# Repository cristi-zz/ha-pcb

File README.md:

## Home automation PCB

The story behind this, can be found [on my blog](https://visoft.ro/hello/expanding-the-stack-designing-a-pcb/2023/01/11/)

It will hold a series of breakout boards for I2C IO expanders, 1Wire drivers, ADCs. All are controlled with a Raspberry Pi 3B+.

The 220V actuators are controlled by a board with 16 mechanical relays. The board is in turn controlled by PCF8575 chip that takes I2C commands and controls 16 I/O pins. Board is active on low (optocouplers), PCF8575 can sink more current (than it could source). Perfect match.

The 16 relay board is separate, from this PCB, only a pin header connection is made.

The temperature sensors are DS18B20 that work on 1 wire protocol. These are already mounted with Ethernet cables terminated with RJ45. The sensors are read/driven by 4 ds2482s-100 chips (RJ45 terminals and ds2482s-100 are on this PCB).
The RJ jacks must be galvanic!

There are some other relays/contactors/voltages that needs monitoring, all done by 2 ADS1115 16-Bit ADC, present on board.

The chips are already sourced and live on their breakout boards. The PCB is mainly THT because of sourcing issues (eg can't find ds2482s-100 anywhere, will reuse existing breakouts). Only SMD are the 3.5 audio jacks (for ADC) again because no THT could be sourced atm.

The Raspberry Pi connector is only 20 pin wide because only the first few are used (5V, 3.3, SDA, SCL, GND)

There is a spurious bug, all relays are ON when the 16 relay board is powered but the Raspberry (that powers the rest of the circuits) is OFF. So, a solid state relay is used to cut power to the relay board when the RaPi is shutted down.

With the exception of ADCs, the schema and design choices follow the existing (4 years old) system.

This repo is mainly for reviewing purposes.

**The story behind this PCB is on [www.visoft.ro](https://www.visoft.ro/beginner/expanding-the-stack-designing-a-pcb/2372/)**

A list with the devices

### Relay board that will be driven:
https://www.sainsmart.com/products/16-channel-12v-relay-module

### 16 channel IO expander that will drive the board:
https://www.artekit.eu/products/breakout-boards/io/ak-pcf8575-i2c-16-bit-io-expander-breakout/

### I2C level shifter (3.3 to 5V)
https://www.pololu.com/product/2595

### I2C to differential signals:
https://www.sparkfun.com/products/retired/14589

### 1Wire drivers:
https://www.artekit.eu/products/breakout-boards/io/ak-ds2482s-100/

### ADC:
https://www.adafruit.com/product/1085

Some ADC "watch" only for presence/absence of 5V power but some are listenting to CT sensors.
Quasi similar model: https://www.seeedstudio.com/Non-invasive-AC-Current-Sensor-30A-ma-p-519.html

### Solid state relay:
https://www.tme.eu/en/details/dmo063/dc-solid-state-relays/crydom/

Add comments here (as git issues) or on EEVBlog.

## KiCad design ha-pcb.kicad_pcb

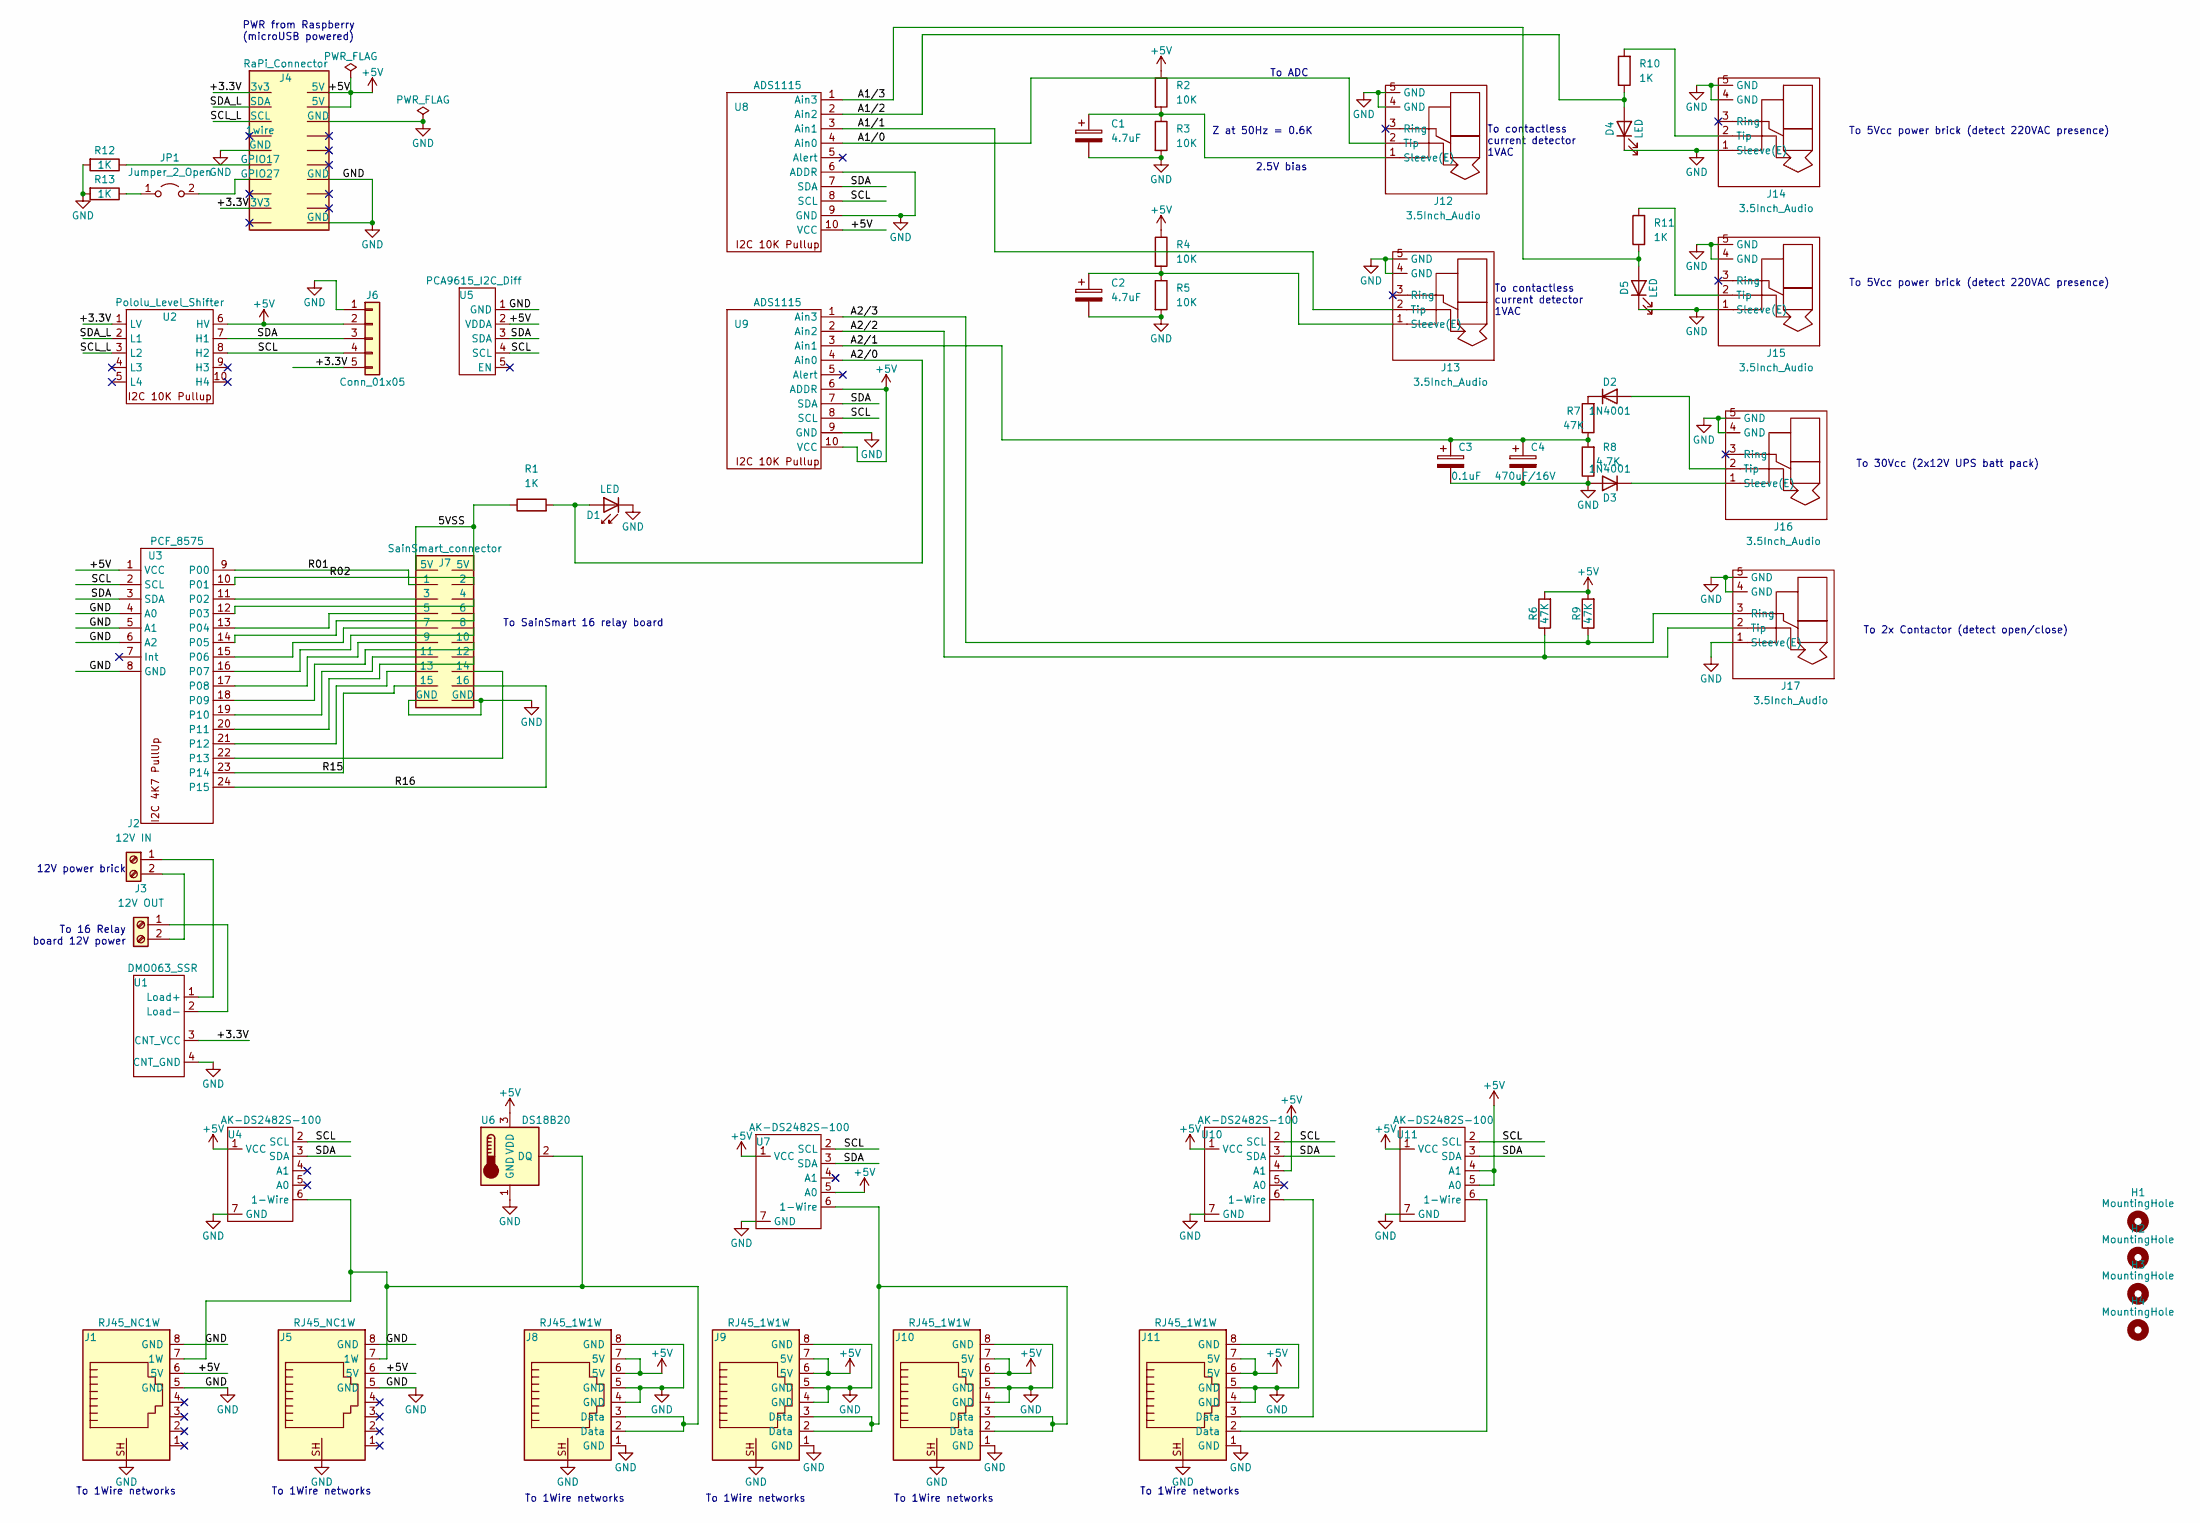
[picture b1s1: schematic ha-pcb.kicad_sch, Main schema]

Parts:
C1, C2: 4.7uF; CP_Radial_D4.0mm_P2.00mm
C3: 0.1uF; CP_Radial_D4.0mm_P2.00mm
C4: 470uF/16V; CP_Radial_D8.0mm_P3.80mm
D1, D4, D5: LED; LED_D5.0mm
D2, D3: 1N4001; D_DO-41_SOD81_P10.16mm_Horizontal
H1, H2, H3, H4: MountingHole; MountingHole_2.5mm
J1, J5: RJ45_NC1W; RJ45_Ninigi_GE_silver
J2: 12V IN; TerminalBlock_RND_205-00001_1x02_P5.00mm_Horizontal
J3: 12V OUT; TerminalBlock_RND_205-00001_1x02_P5.00mm_Horizontal
J4: RaPi_Connector; PinHeader_2x10_P2.54mm_Vertical
J6: Conn_01x05; PinHeader_1x05_P2.54mm_Vertical
J7: SainSmart_connector; PinHeader_2x10_P2.54mm_Vertical
J8, J9, J10, J11: RJ45_1W1W; RJ45_Ninigi_GE_silver
J12, J13, J14, J15, J16, J17: 3.5Inch_Audio; 3.5mmJack SMD
JP1: Jumper_2_Open; PinHeader_1x02_P2.54mm_Vertical
R1, R10, R11, R12, R13: 1K; R_Axial_DIN0207_L6.3mm_D2.5mm_P10.16mm_Horizontal
R2, R3, R4, R5: 10K; R_Axial_DIN0207_L6.3mm_D2.5mm_P10.16mm_Horizontal
R6, R7, R9: 47K; R_Axial_DIN0207_L6.3mm_D2.5mm_P10.16mm_Horizontal
R8: 4.7K; R_Axial_DIN0207_L6.3mm_D2.5mm_P10.16mm_Horizontal
U1: DMO063_SSR
U2: Pololu_Level_Shifter; Pololu Level Shifter
U3: PCF_8575
U4, U7, U10, U11: AK-DS2482S-100
U5: PCA9615_I2C_Diff; PinHeader_1x05_P2.54mm_Vertical
U6: DS18B20; TO-92_Inline_Wide
U8, U9: ADS1115

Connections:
+5V: J1.6 (5V), J4.2 (5V), J4.4 (5V), J5.6 (5V), J6.2, J8.6 (5V), J8.7 (5V), J9.6 (5V), J9.7 (5V), J10.6 (5V), J10.7 (5V), J11.6 (5V), J11.7 (5V), R2.1, R4.1, R6.2, R9.2, U2.6 (HV), U3.1 (VCC), U4.1 (VCC), U5.2 (VDDA), U6.3 (VDD), U7.1 (VCC), U7.5 (A0), U8.10 (VCC), U9.6 (ADDR), U9.10 (VCC), U10.1 (VCC), U10.4 (A1), U11.1 (VCC), U11.4 (A1), U11.5 (A0)
/5VSS: J7.1 (5V), J7.2 (5V), R1.1
/+3.3V: J4.1 (3v3), J4.17 (3V3), J6.5, U1.3 (CNT_VCC), U2.1 (LV)
/A1/0: J12.2 (Tip), U8.4 (Ain0)
/A1/1: J13.2 (Tip), U8.3 (Ain1)
/A1/2: D4.2 (A), R10.1, U8.2 (Ain2)
/A1/3: D5.2 (A), R11.1, U8.1 (Ain3)
/A2/0: D1.2 (A), R1.2, U9.4 (Ain0)
/A2/1: C3.1, C4.1, R7.1, R8.2, U9.3 (Ain1)
/A2/2: J17.2 (Tip), R6.1, U9.2 (Ain2)
/A2/3: J17.3 (Ring), R9.1, U9.1 (Ain3)
/R01: J7.3 (1), U3.9 (P00)
/R02: J7.4 (2), U3.10 (P01)
/R15: J7.17 (15), U3.23 (P14)
/R16: J7.18 (16), U3.24 (P15)
/SCL: J6.4, U2.8 (H2), U3.2 (SCL), U4.2 (SCL), U5.4 (SCL), U7.2 (SCL), U8.8 (SCL), U9.8 (SCL), U10.2 (SCL), U11.2 (SCL)
/SCL_L: J4.5 (SCL), U2.3 (L2)
/SDA: J6.3, U2.7 (H1), U3.3 (SDA), U4.3 (SDA), U5.3 (SDA), U7.3 (SDA), U8.7 (SDA), U9.7 (SDA), U10.3 (SDA), U11.3 (SDA)
/SDA_L: J4.3 (SDA), U2.2 (L1)
GND: C1.2, C2.2, C3.2, C4.2, D1.1 (K), D3.2 (A), D4.1 (K), D5.1 (K), J1.5 (GND), J1.8 (GND), J1.SH, J4.6 (GND), J4.9 (GND), J4.14 (GND), J4.20 (GND), J5.5 (GND), J5.8 (GND), J5.SH, J6.1, J7.19 (GND), J7.20 (GND), J8.1 (GND), J8.4 (GND), J8.5 (GND), J8.8 (GND), J8.SH, J9.1 (GND), J9.4 (GND), J9.5 (GND), J9.8 (GND), J9.SH, J10.1 (GND), J10.4 (GND), J10.5 (GND), J10.8 (GND), J10.SH, J11.1 (GND), J11.4 (GND), J11.5 (GND), J11.8 (GND), J11.SH, J12.4 (GND), J12.5 (GND), J13.4 (GND), J13.5 (GND), J14.1 (Sleeve(E)), J14.4 (GND), J14.5 (GND), J15.1 (Sleeve(E)), J15.4 (GND), J15.5 (GND), J16.4 (GND), J16.5 (GND), J17.1 (Sleeve(E)), J17.4 (GND), J17.5 (GND), R3.2, R5.2, R8.1, R12.2, R13.2, U1.4 (CNT_GND), U3.4 (A0), U3.5 (A1), U3.6 (A2), U3.8 (GND), U4.7 (GND), U5.1 (GND), U6.1 (GND), U7.7 (GND), U8.6 (ADDR), U8.9 (GND), U9.9 (GND), U10.7 (GND), U11.7 (GND)
unnamed: C1.1, J12.1 (Sleeve(E)), R2.2, R3.1
unnamed: C2.1, J13.1 (Sleeve(E)), R4.2, R5.1
unnamed: D2.1 (K), R7.2
unnamed: D2.2 (A), J16.2 (Tip)
unnamed: D3.1 (K), J16.1 (Sleeve(E))
unnamed: J1.7 (1W), J5.7 (1W), J8.2 (Data), J8.3 (Data), U4.6 (1-Wire), U6.2 (DQ)
unnamed: J2.1, U1.1 (Load+)
unnamed: J2.2, J3.2
unnamed: J3.1, U1.2 (Load-)
unnamed: J4.11 (GPIO17), R12.1
unnamed: J4.13 (GPIO27), JP1.2 (B)
unnamed: J7.5 (3), U3.11 (P02)
unnamed: J7.6 (4), U3.12 (P03)
unnamed: J7.7 (5), U3.13 (P04)
unnamed: J7.8 (6), U3.14 (P05)
unnamed: J7.9 (7), U3.15 (P06)
unnamed: J7.10 (8), U3.16 (P07)
unnamed: J7.11 (9), U3.17 (P08)
unnamed: J7.12 (10), U3.18 (P09)
unnamed: J7.13 (11), U3.19 (P10)
unnamed: J7.14 (12), U3.20 (P11)
unnamed: J7.15 (13), U3.21 (P12)
unnamed: J7.16 (14), U3.22 (P13)
unnamed: J9.2 (Data), J9.3 (Data), J10.2 (Data), J10.3 (Data), U7.6 (1-Wire)
unnamed: J11.2 (Data), U11.6 (1-Wire)
unnamed: J11.3 (Data), U10.6 (1-Wire)
unnamed: J14.2 (Tip), R10.2
unnamed: J15.2 (Tip), R11.2
unnamed: JP1.1 (A), R13.1

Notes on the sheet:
To ADC
Z at 50Hz = 0.6K
To 5Vcc power brick (detect 220VAC presence)
PWR from Raspberry (microUSB powered)
To 1Wire networks
To 30Vcc (2x12V UPS batt pack)
To contactless current detector 1VAC
2.5V bias
12V power brick
To 16 Relay board 12V power
To 2x Contactor (detect open/close)
To SainSmart 16 relay board

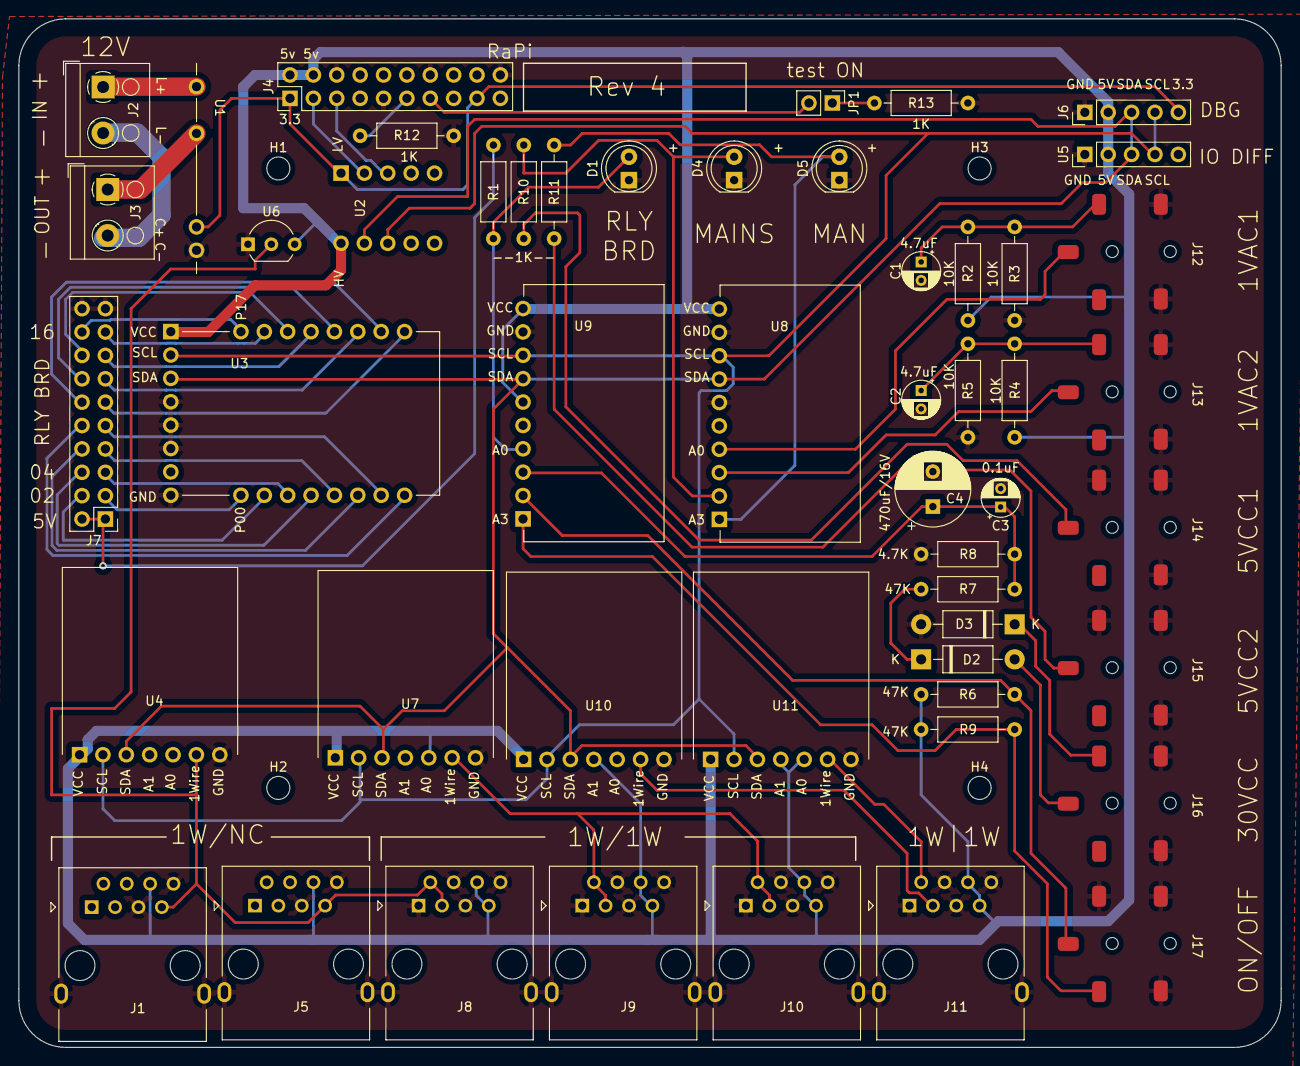
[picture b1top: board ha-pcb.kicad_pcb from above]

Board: 2 copper layers, 137.2 x 111.8 mm, 55 parts (0 on the bottom side), 49 nets.

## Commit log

2022-03-09 Initial commit of ver3 board
2022-03-09 Added readme
2022-03-09 Updated readme with more details
2022-03-09 Added info about the SSR
2022-03-11 Incorporated feedback from forum.\nAdded two GPIOs for test marking
2022-03-11 regenerated gerbers
2022-03-16 Sent pcb to manufacturer step 1
2023-01-11 Insert image in readme.
2024-01-07 Update README.md
    Backlink to blog
